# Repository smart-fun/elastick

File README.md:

# Elastick adapter

Connect vintage joysticks (Apple II, Atari, CoCo, Sega…) to a modern PC via Bluetooth.

🚧 WORK IN PROGRESS – NOT READY YET 🚧

Elastick is a hardware and software project built around the ESP32‑based Lolin D32.

It interfaces with classic joysticks and exposes them as standard Bluetooth game controllers, compatible with emulators like MAME or with any modern game supporting gamepads.

Vintage controllers can also be tested directly on the Elastick device itself, without needing a Bluetooth connection.

## Supported Controllers

**Josticks / Game Pads**

- Amstrad CPC
- Apple II - with a cable adapter
- Atari 8 bits / ST
- Commodore 64/128/Amiga
- IBM PC (DA-15 connector) - with a cable adapter
- MSX
- Sega Master System
- Sega Mega Drive
- Tandy Color Computer (CoCo) - with a cable adapter
- Thomson MO/TO - with a cable adapter

**Mouses**

- Amiga Mouse (test only)
- Atari ST Mouse (test only)

**Paddles**

- Atari 2600 Paddles

## Installation

The main code is located in the code/elastick folder. The project now works with **VSCode IDE + PlatformIO** extension. Simply open this folder from the PlatformIO extension, build and upload on the Elastick board!

The main folders:

- **code**: arduino code
- **3d**: resources for 3D printing (not ready yet)
- **elec**: kicad project for PCB
- **resources**: various pictures

## Known issues

#### Devices requiring 5V power

Most devices work without using the VCC pin at all, but a few peripherals need a full 5‑volt supply to operate correctly. Since the Arduino only provides 3.3 V, these devices may fail to initialize or behave unpredictably.
So far, only one mouse has shown this limitation; all other tested devices function normally.

#### ESP32 reboot during Bluetooth initialization

Some ESP32 boards (including the Lolin D32) may reboot exactly when Bluetooth is initialized.

After investigation, the root cause was a **regression in the ESP32 Arduino core (version 3.x)** affecting BLE initialization. The board consistently reboots as soon as Bluetooth is started. Using the **ESP32 Arduino core 2.0.17** restores full stability:

- no reboot during BLE initialization
- stable operation on USB power or on battery

Using ESP32 Arduino core 2.0.17 fully resolves this issue.

## Hardware

- [Lolin D32 WROOM (ESP32) µc](https://fr.aliexpress.com/item/1005006233798203.html)
- [OLED 0,96" SSD1306 I2C 128X64 pixels](https://fr.aliexpress.com/item/1005004355547926.html)
- [DE-9 female connector](https://fr.aliexpress.com/item/1005006997365476.html) aka DB9
- [Rotary Button EC11](https://fr.aliexpress.com/item/1005007737001031.html)

## Additional documentation

- [Controllers pinout](/resources/controllers_pinout.md)

## License

**This project was originally released under the MIT License. As of April 2026, it is distributed under the Apache License 2.0.**

Copyright 2026 Arnaud Guyon

Licensed under the Apache License, Version 2.0 (the "License");
you may not use this file except in compliance with the License.
You may obtain a copy of the License at

    http://www.apache.org/licenses/LICENSE-2.0

Unless required by applicable law or agreed to in writing, software
distributed under the License is distributed on an "AS IS" BASIS,
WITHOUT WARRANTIES OR CONDITIONS OF ANY KIND, either express or implied.
See the License for the specific language governing permissions and
limitations under the License.

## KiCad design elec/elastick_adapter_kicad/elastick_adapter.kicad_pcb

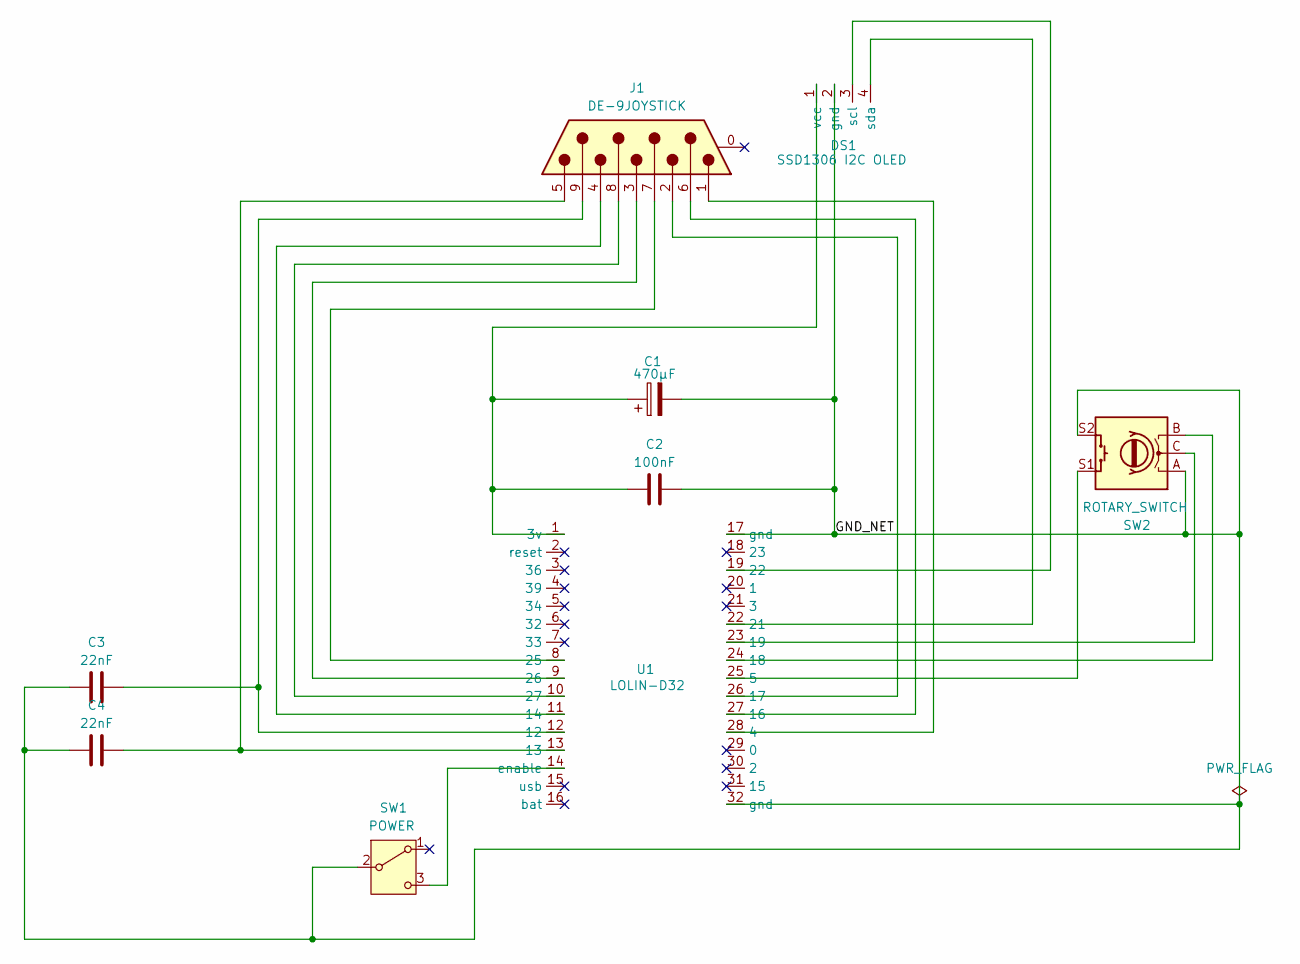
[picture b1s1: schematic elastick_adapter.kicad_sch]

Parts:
C1: 470µF; CP_Radial_D8.0mm_P3.50mm
C2: 100nF; C_Disc_D5.0mm_W2.5mm_P5.00mm
C3, C4: 22nF; C_Disc_D5.0mm_W2.5mm_P5.00mm
DS1: SSD1306 I2C OLED; oled_128_64_i2c
J1: DE-9JOYSTICK; DSUB-9_Pins_Horizontal_P2.77x2.84mm_EdgePinOffset7.70mm_Hou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
SW1: POWER; SW_90degrees_3pins
SW2: ROTARY_SWITCH; rotary_encoder
U1: LOLIN-D32; Lolin D32

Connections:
/GND_NET: C1.2, C2.2, C3.1, C4.1, DS1.2 (gnd), SW1.2 (B), SW2.A, SW2.S2, U1.17 (gnd), U1.32 (gnd)
unnamed: C3.2, J1.9, U1.12
unnamed: C4.2, J1.5, U1.13
unnamed: DS1.3 (scl), U1.19 (22)
unnamed: DS1.4 (sda), U1.22 (21)
unnamed: C1.1, C2.1, DS1.1 (vcc), U1.1 (3v)
unnamed: SW1.3 (C), U1.14 (enable)
unnamed: J1.1, U1.28 (4)
unnamed: SW2.S1, U1.25 (5)
unnamed: J1.4, U1.11 (14)
unnamed: J1.6, U1.27 (16)
unnamed: J1.2, U1.26 (17)
unnamed: SW2.B, U1.24 (18)
unnamed: SW2.C, U1.23 (19)
unnamed: J1.7, U1.8 (25)
unnamed: J1.3, U1.9 (26)
unnamed: J1.8, U1.10 (27)

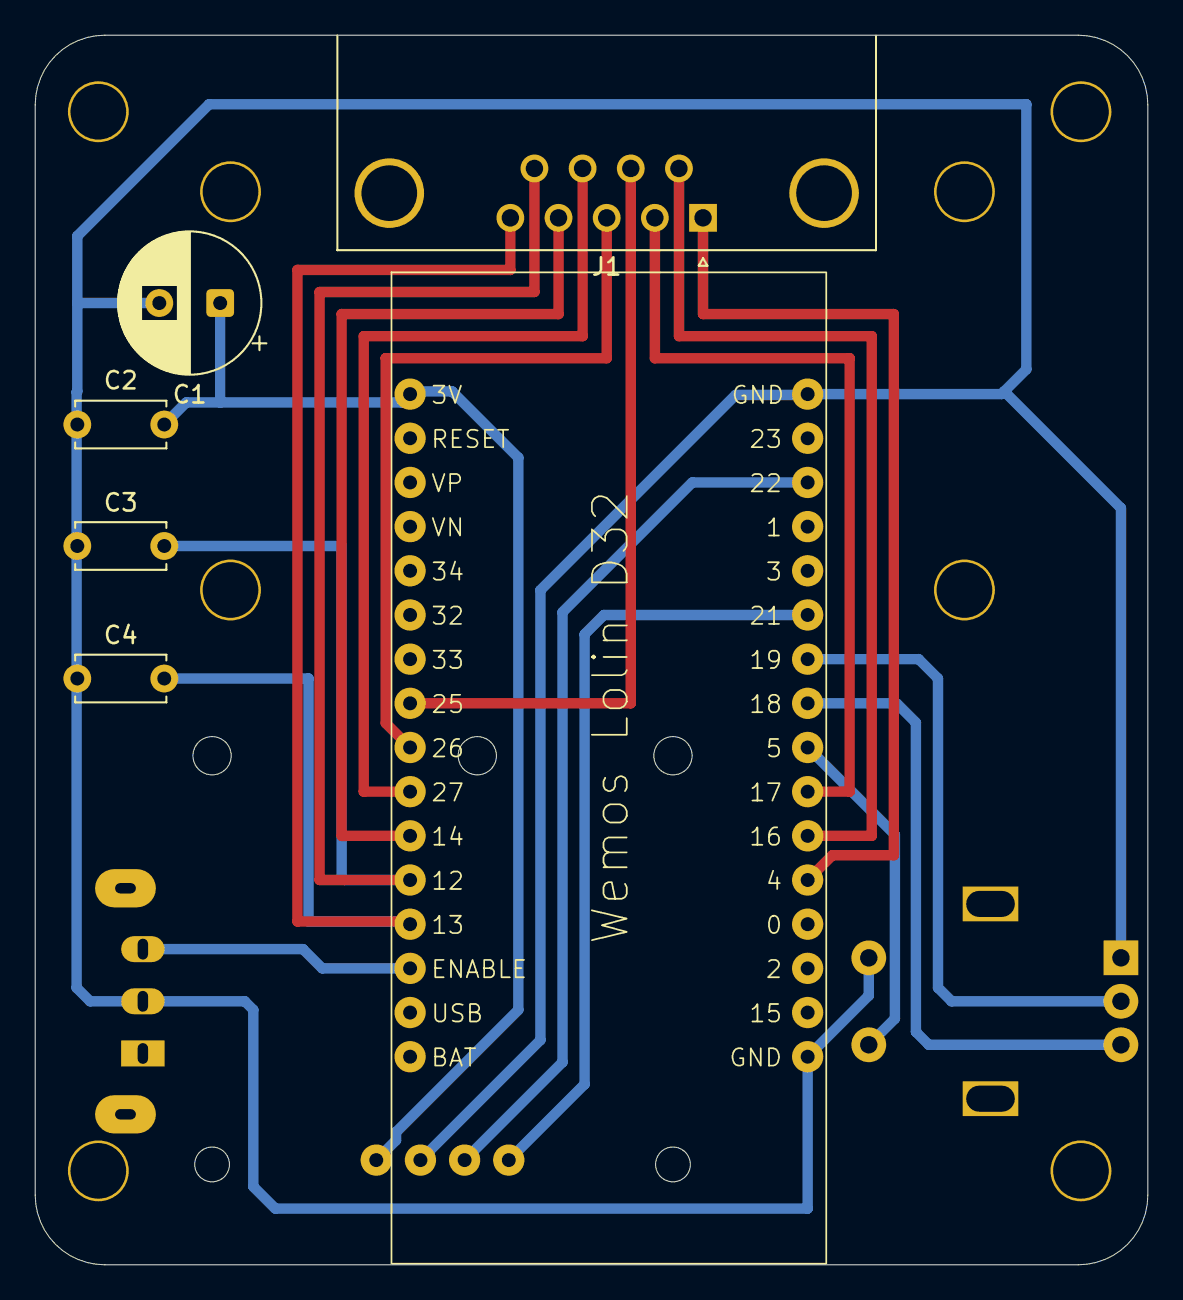
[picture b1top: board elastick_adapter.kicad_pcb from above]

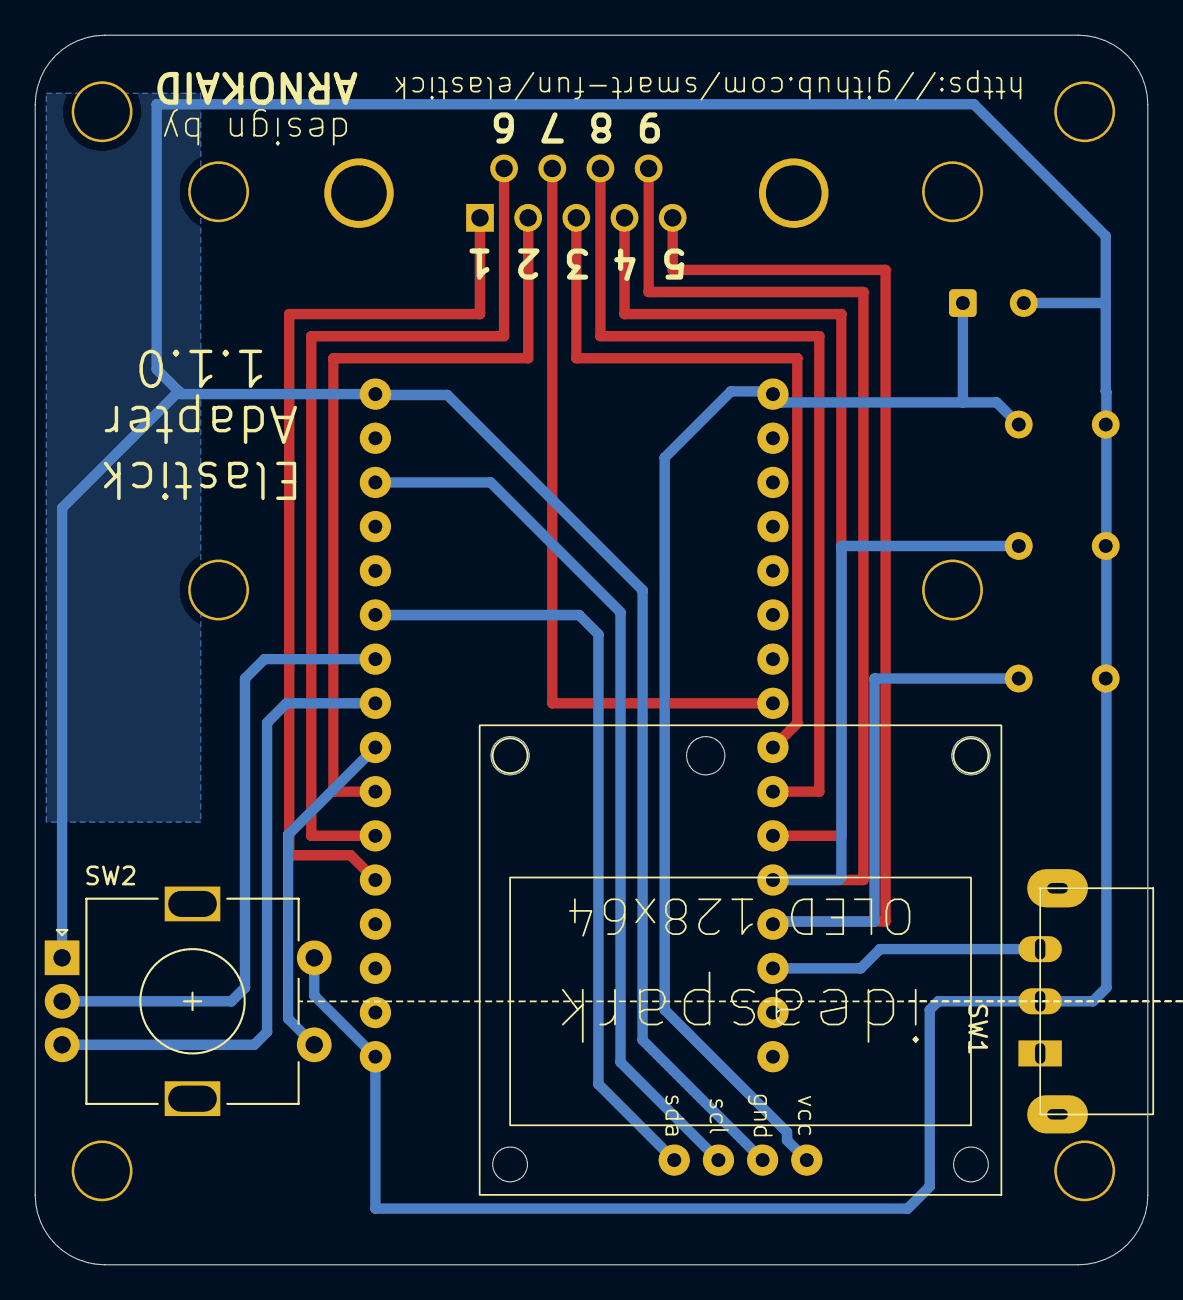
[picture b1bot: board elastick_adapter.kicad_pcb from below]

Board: 2 copper layers, 64.0 x 70.7 mm, 9 parts (3 on the bottom side), 17 nets.

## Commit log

2025-08-02 add BleGamepad sample code
2025-08-02 update documentation
2025-08-04 basic atari joystick with 1 button working (hardcoded test)
2025-08-09 tests & tuning for atari analog paddles
2025-08-09 start organizing code
2025-08-09 ability to switch between Atari 2600 joystick or paddle, using modulable mappings
2025-08-21 update documentation with joystick pictures
2025-08-22 Update joystick documentation for Amstrad and Thomson
2025-08-22 update documentation with MSX and Sega Master System
2025-08-24 added code sample to detect if apple 2 joystick is plugged correctly + new method for reading analog joysticks using charging/discharging capacitor duration (like it was in the 70s-80s).
2025-08-25 move code to subfolders. Add InputButtons and DisplayManager classes
2025-08-26 display controller (short) list
2025-08-26 add menu navigation and interaction architecture.
2025-08-26 add welcome menu + navigate from welcome menu to controller list menu
2025-08-27 add (empty) Action Menu
2025-08-27 add controller detection phase (not implemented yet)
2025-08-27 add real apple 2 detection. disabled all bluetooth stuff in order to no interact with the menus
2025-08-28 add PLAY, CALIBRATE, TEST in Action Menu
2025-08-28 add PinConfig for Play mode (not only Detection mode)
2025-08-28 init controller and log pin values when PLAY is chosen
2025-08-28 add Amiga / Atari / C64 / CPC controller (same for all)
2025-08-29 add test mode (wip)
2025-08-29 add Apple II read axis and buttons
2025-08-29 display joystick and buttons in test mode
2025-08-29 put Test features into a new TestMenu class
2025-08-29 remove almost all dynamic allocation to try to not reboot when starting BLE
2025-08-30 workaround for auto-reboot when starting BLE for the first time. first really playable version
2025-08-30 can go back to controler list. avoid to recreate Action Items.
2025-08-30 add Atari Paddles read methods
2025-08-30 fixed atari/cpc y axis value
2025-08-30 add ibm pc read values. top ble just before 1st reboot
2025-08-30 add msx controller. provide an idle behaviour if validate button is pressed during boot (easier to flash formware when no bluetooth or anything is started)
2025-08-30 rename files without "es" prefix. add some missing include.
2025-08-30 add Tandy CoCo controller
2025-09-05 add kicad project for PCB (wip)
2025-09-06 added time compensation when buttons are pressed
2025-09-06 start cleanup
2025-09-06 fixed issues with coco joystick with values around center of axis
2025-09-11 update kicad
2025-09-13 Replaced Next and Validate buttons with Rotary Switch.
2025-09-13 update test programs
2025-09-13 fixed crash in menus. declare atari & msx as digital controllers.
2025-09-14 number of buttons & axis more flexible, even if hardware only supports 2x2 yet
2025-09-14 update kicad with 3d for rotary button
2025-09-21 update pinout for new hardware. changed "play" to "connect to pc". set number of axis to 2 for ibm & paddle controllers.
2025-10-04 elec: last changes before order 1.0.0
2025-10-19 add test code
2025-10-26 Split GameController into AnalogGameController and DigitalGameController. Display analog values in "test" menu.
2025-11-01 add Sega Master System joypad
2025-11-01 add Thomson MO/TO controller
2026-02-21 Add Sega Mega Drive controllers
2026-02-21 tuning for mega drive controller
2026-02-21 update documentation (as github does not display colors)
2026-02-21 Update README with important Bluetooth bug fix
2026-02-21 Fixed rotary input
2026-02-22 Improved Menus.
2026-02-22 Add test for Amiga Mouse
2026-02-22 add Amiga Mouse Controller (1st version)
2026-02-24 add MouseController class so that it will be easier to add other mouses like Atari mouses
2026-02-26 migrate project from arduino IDE to vscode
2026-02-26 organise files in subfolders (menus / controllers)
2026-02-26 clone Atari controller to get Amiga + C64 + Amstrad different entries
2026-02-28 add ListMenu to handle all menus with lists the same way
2026-02-28 improve menus for better and unified navigation (WIP)
2026-02-28 still refactoring menus (WIP)
2026-02-28 still menu refacto WIP
2026-02-28 stabilize menus
2026-02-28 update battery percent
2026-03-01 Update readme picture
2026-03-01 make pcb more compact (+ removed usb-c adapter)
2026-03-02 specify platform version in platformio.ini to be sure it uses an Arduino Core 2.x
2026-03-05 refactor: move global state to class members in controller classes
    Convert global variables in MegaDriveController and MouseController to private class members for better encapsulation and safety. Use static instance pointer pattern in MouseController to allow inter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
2026-03-05 PCB: display pin numbers for DB9
2026-03-06 improved controller reactivity. removed smoothed values on atari paddle as the values are stable.
2026-03-10 update documentation with video link
2026-04-06 Changed LICENSE from MIT to Apache 2.0
